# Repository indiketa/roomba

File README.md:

# roomba
Fa uns mesos que tenim una persona que vé a casa i ens ajuda amb les feines... n'estem molt contents però darrerament sospitem que s'hi està molt menys temps del que hem pactat. Vé quan som fora i no tenim forma de saber quan de temps s'hi està... Sempre havia volgut fer alguna cosa amb arduino: ara n'he tingut l'excusa.

Aquest projecte és una xorrada: Si busques grans desenvolupaments o descobriments t'has equivocat de repositori (i d'usuari)! 
Això és un simple divertimento.

Com que tampoc volía complicar-me la vida (i arriscar-me a fer alguna cosa que no funcionés), vaig decidir muntar el projecte envers a una resistencia LDR: Un tipus de resistència que varia en funció de la llum que hi ha a l'entorn. La idea és situar això a prop de l'entrada, cada vegada que s'obri la porta del carrer la llum variarà de forma notòria, ho detectarem i ens ho guardarem en un registre de text.

Per controlar això hem fet servir una arduino petita xina que hem [trobat](https://www.amazon.es/dp/B01M7ZB2B4?aaxitk=gaqGsul2mgWlRdqk36D8Dw&pd_rd_i=B01M7ZB2B4&pf_rd_p=b4a87efe-46df-474d-b505-3bf1bb51624b&hsa_cr_id=9182184180602&sb-ci-n=productDescription&sb-ci-v=Elegoo%20UNO%20R3%20Tarjeta%20UNO%20R3%20Placa%20con%20Microcontrolador%20Basada%20en%20el%20ATmega328P%20ATMEGA16U2%20con%20Cable%20USB%20Compatible%20con%20Arduino%20UNO%20Tarjeta) a l'amazon!

Després d'estar-ho mirant m'adono que l'arduino no té RTC (real time clock) i que de poc ens servrà si no podem saber l'hora, per aquest motiu, vaig comprar també un mòdul RTC que em permeti saber l'hora actual: vaig comprar [aquest](https://www.amazon.es/WINGONEER-DS3231-AT24C32-precisi%C3%B3n-Arduino/dp/B01H5NAFUY/ref=sr_1_5?ie=UTF8&qid=1544285193&sr=8-5&keywords=Arduino+Rtc), com que no en sóc cap expert... simplement et diré que dona la hora i la data correctament: Potser la llibreria per tractar-ho es menja molta memòria, rellegint-la per sobre hi ha molt de codi que es podria eliminar i en aquest projecte tot continuaria funcionant.

Ara que ja sabem mesurar la llum i sabem l'hora que és... falta un lloc on desar-ho- com que ho volia tenir ràpid, en comptes d'enviar coses per wifi i haver de tenir algun servei escoltant en alguna banda vaig decidir gravar-ho en una SD local (en plan datalogger). Per aquest motiu vaig afegir-hi un microSD Adapter per aduino... [aquest](https://www.ebay.es/i/272536699694?chn=ps)

Ara sí, ja ho tenim tot, dissenyem el circuit amb l'eagle:

Primer vaig provar-ho tot en una protoboard i va funcionar, però el manyoc de cables per no fer res era considerable. Total que vaig decidir fer-me la placa amb l'EAGLE i fer-la imprimir per internet.La vaig imprimir a https://www.seeedstudio.io:

No és el millor disseny ho sé, el proper invent el farem millor. 

I bàsicament així es com va quedar tot muntat:

I acoplat a la arduino uno:

Com veieu, al fi i al cap, controlar les hores era el menys important ;)
El cost final del projecte van ser 10€ per l'arduino, 3€ per l'RTC, 3€ per la controladora SD, 5€ per la placa (mínim 5 copies, me'n sobren 4 si algú les vol), i la resistencia LDR no ho sé: cèntims d'euro.

I vet aquí un gat i vet aquí un gos, que aquest compte ja s'ha fos.

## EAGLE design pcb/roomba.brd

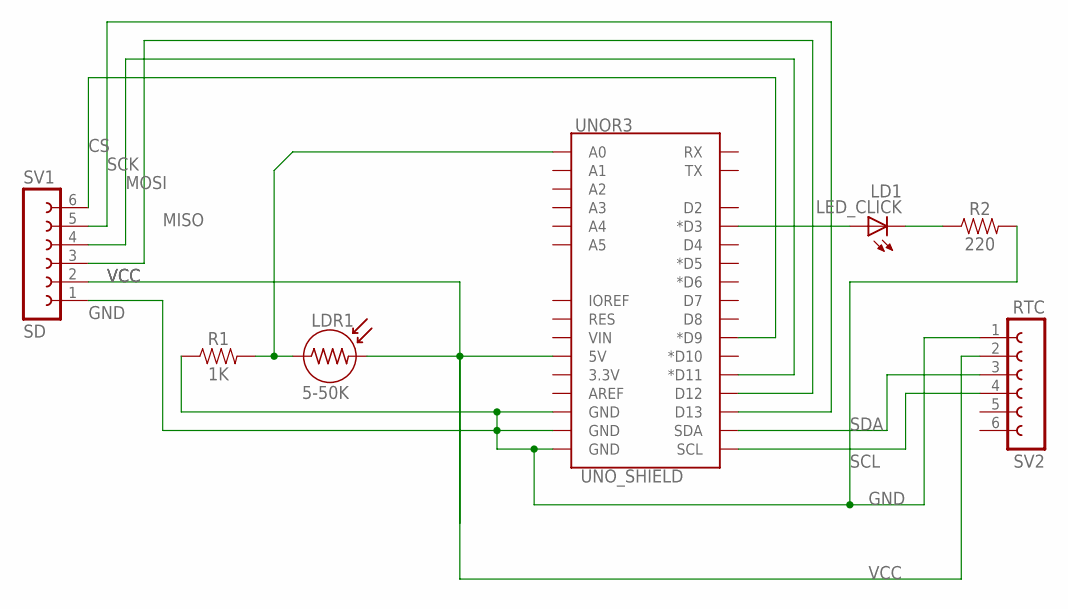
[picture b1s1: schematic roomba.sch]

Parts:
LDR1: 5-50K; LDR
LED_CLICK: LD1; LED3MM
R1: 1K; AXIAL-0.3
R2: 220; AXIAL-0.3
SV1: SD; FE06
SV2: RTC; FE06W
UNOR3: UNO_SHIELD; UNO_R3_SHIELD_NOLABELS

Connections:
CLICK: LED_CLICK.A, UNOR3.D3 (*D3)
CS: SV1.6, UNOR3.D9 (*D9)
GND: R1.P$1 (1), R2.P$2 (2), SV1.1, SV2.1, UNOR3.GND@0 (GND), UNOR3.GND@1 (GND), UNOR3.GND@2 (GND)
LECTURA: LDR1.1, R1.P$2 (2), UNOR3.A0
MISO: SV1.3, UNOR3.D12
MOSI: SV1.4, UNOR3.D11 (*D11)
RCLICK: LED_CLICK.K (C), R2.P$1 (1)
SCK: SV1.5, UNOR3.D13
SCL: SV2.4, UNOR3.SCL
SDA: SV2.3, UNOR3.SDA
VCC: LDR1.2, SV1.2, SV2.2, UNOR3.5V

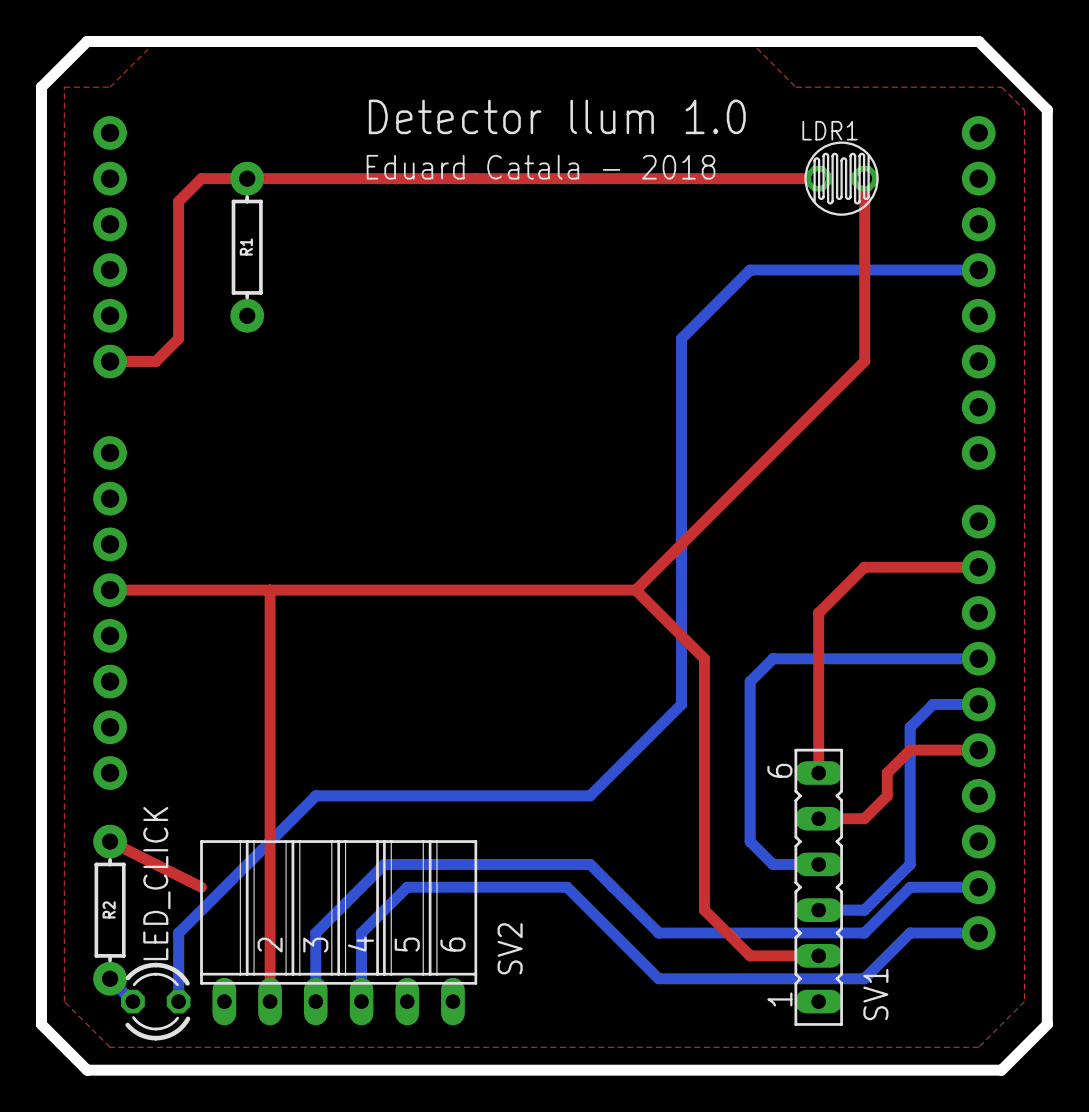
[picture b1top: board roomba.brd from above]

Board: 2 copper layers, 55.9 x 57.2 mm, 7 parts (1 on the bottom side), 11 nets.

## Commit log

2018-12-08 Pujada inicial de codi
2018-12-08 Pujar alguna foto
2018-12-08 Posar 4 fotos

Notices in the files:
parts and their libraries:
SparkFun-Boards: Licensing: Creative Commons ShareAlike 4.0 International - https://creativecommons.org/licenses/by-sa/4.0
